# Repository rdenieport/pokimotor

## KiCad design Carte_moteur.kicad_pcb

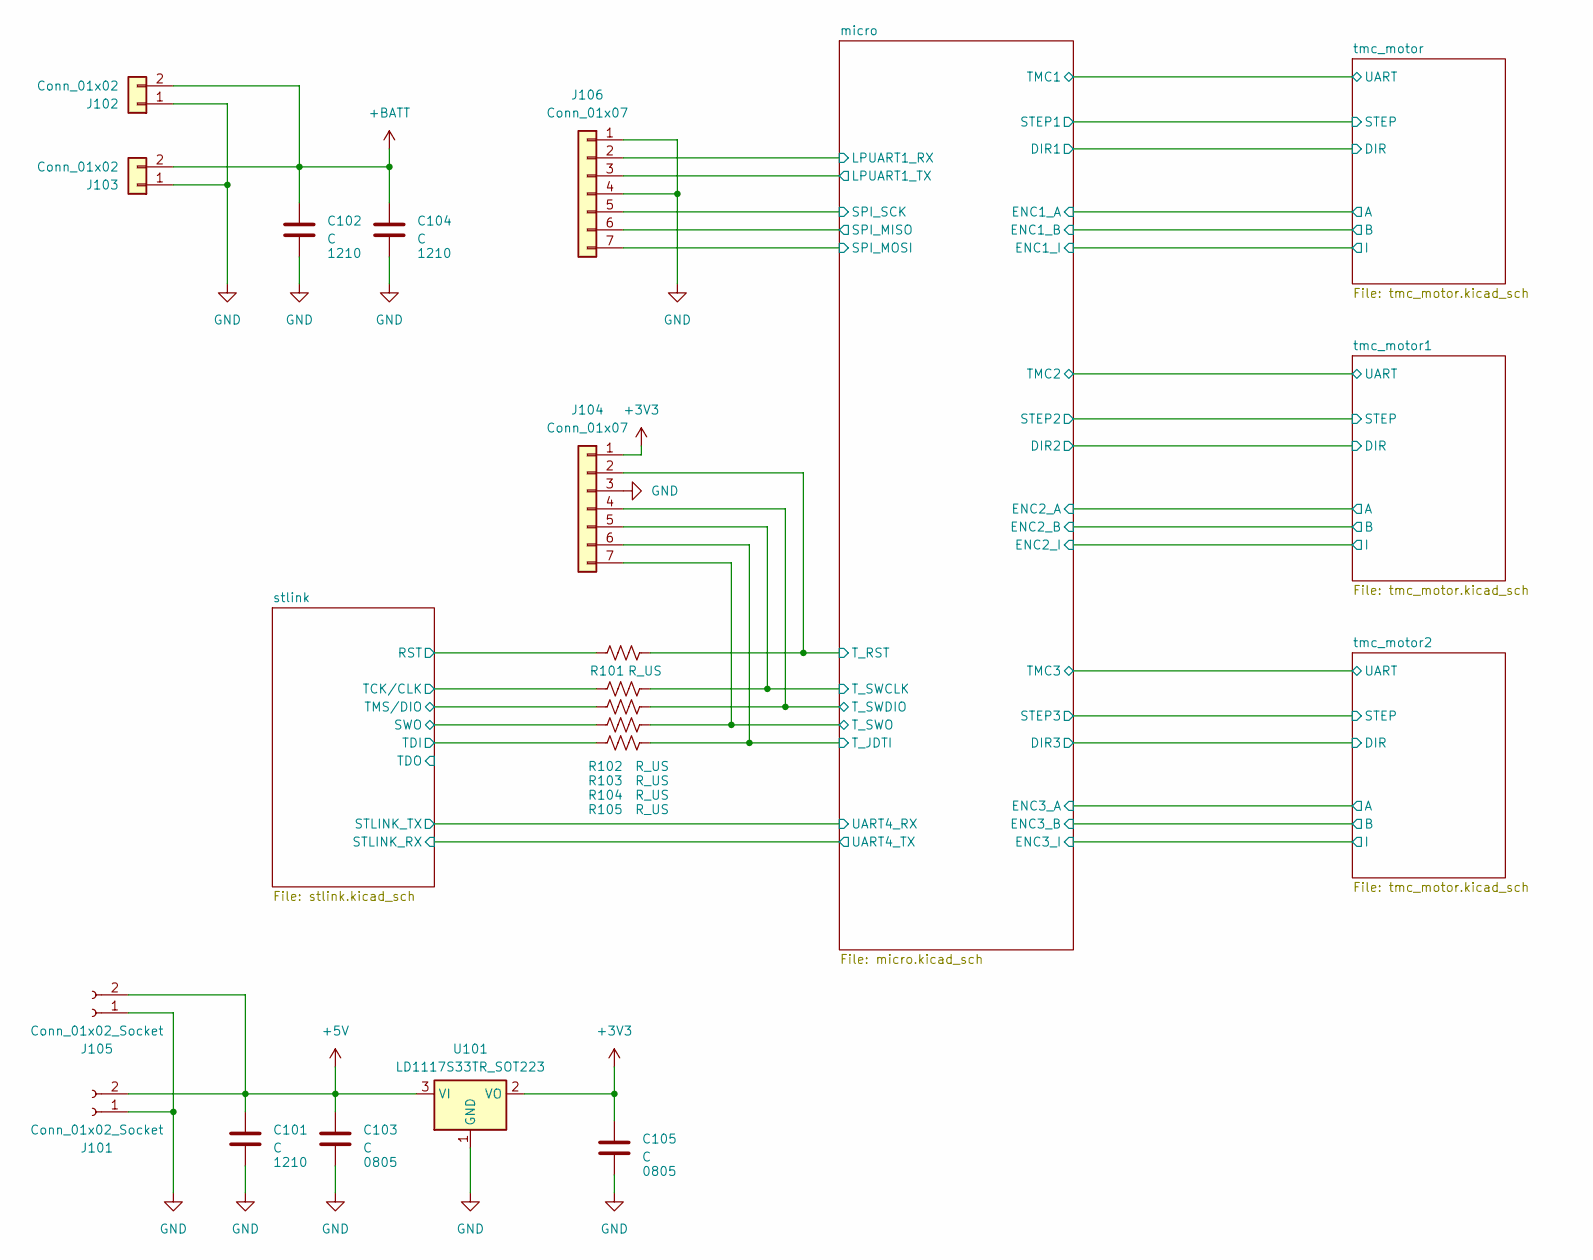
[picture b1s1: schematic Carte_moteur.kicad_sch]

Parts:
C101, C102, C104: C; C_1210_3225Metric_Pad1.33x2.70mm_HandSolder
C103, C105: C; C_0805_2012Metric_Pad1.18x1.45mm_HandSolder
J101, J105: Conn_01x02_Socket; Molex_KK-396_A-41791-0002_1x02_P3.96mm_Vertical
J102, J103: Conn_01x02; Molex_KK-396_A-41791-0002_1x02_P3.96mm_Vertical
J104, J106: Conn_01x07; Molex_KK-254_AE-6410-07A_1x07_P2.54mm_Vertical
R101, R102, R103, R104, R105: R_US; R_0603_1608Metric_Pad0.98x0.95mm_HandSolder
U101: LD1117S33TR_SOT223; SOT-223-3_TabPin2

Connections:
+3V3: C105.1, J104.1, U101.2 (VO); also elsewhere on the board
+5V: C101.1, C103.1, J101.2, J105.2, U101.3 (VI); also elsewhere on the board
+BATT: C102.1, C104.1, J102.2, J103.2; also elsewhere on the board
/micro/LPUART1_RX: J106.2; also elsewhere on the board
/micro/LPUART1_TX: J106.3; also elsewhere on the board
/micro/SPI1_MISO: J106.6; also elsewhere on the board
/micro/SPI1_MOSI: J106.7; also elsewhere on the board
/micro/SPI1_SCK: J106.5; also elsewhere on the board
/micro/T_JDTI: J104.6, R105.1; also elsewhere on the board
/micro/T_RST: J104.2, R101.1; also elsewhere on the board
/micro/T_SWCLK: J104.5, R102.1; also elsewhere on the board
/micro/T_SWDIO: J104.4, R103.1; also elsewhere on the board
/micro/T_SWO: J104.7, R104.1; also elsewhere on the board
/stlink/T_JTCK: R102.2; also elsewhere on the board
/stlink/T_JTDI: R105.2; also elsewhere on the board
/stlink/T_JTMS: R103.2; also elsewhere on the board
/stlink/T_NRST: R101.2; also elsewhere on the board
/stlink/T_SWO: R104.2; also elsewhere on the board
GND: C101.2, C102.2, C103.2, C104.2, C105.2, J101.1, J102.1, J103.1, J104.3, J105.1, J106.1, J106.4, U101.1 (GND); also elsewhere on the board

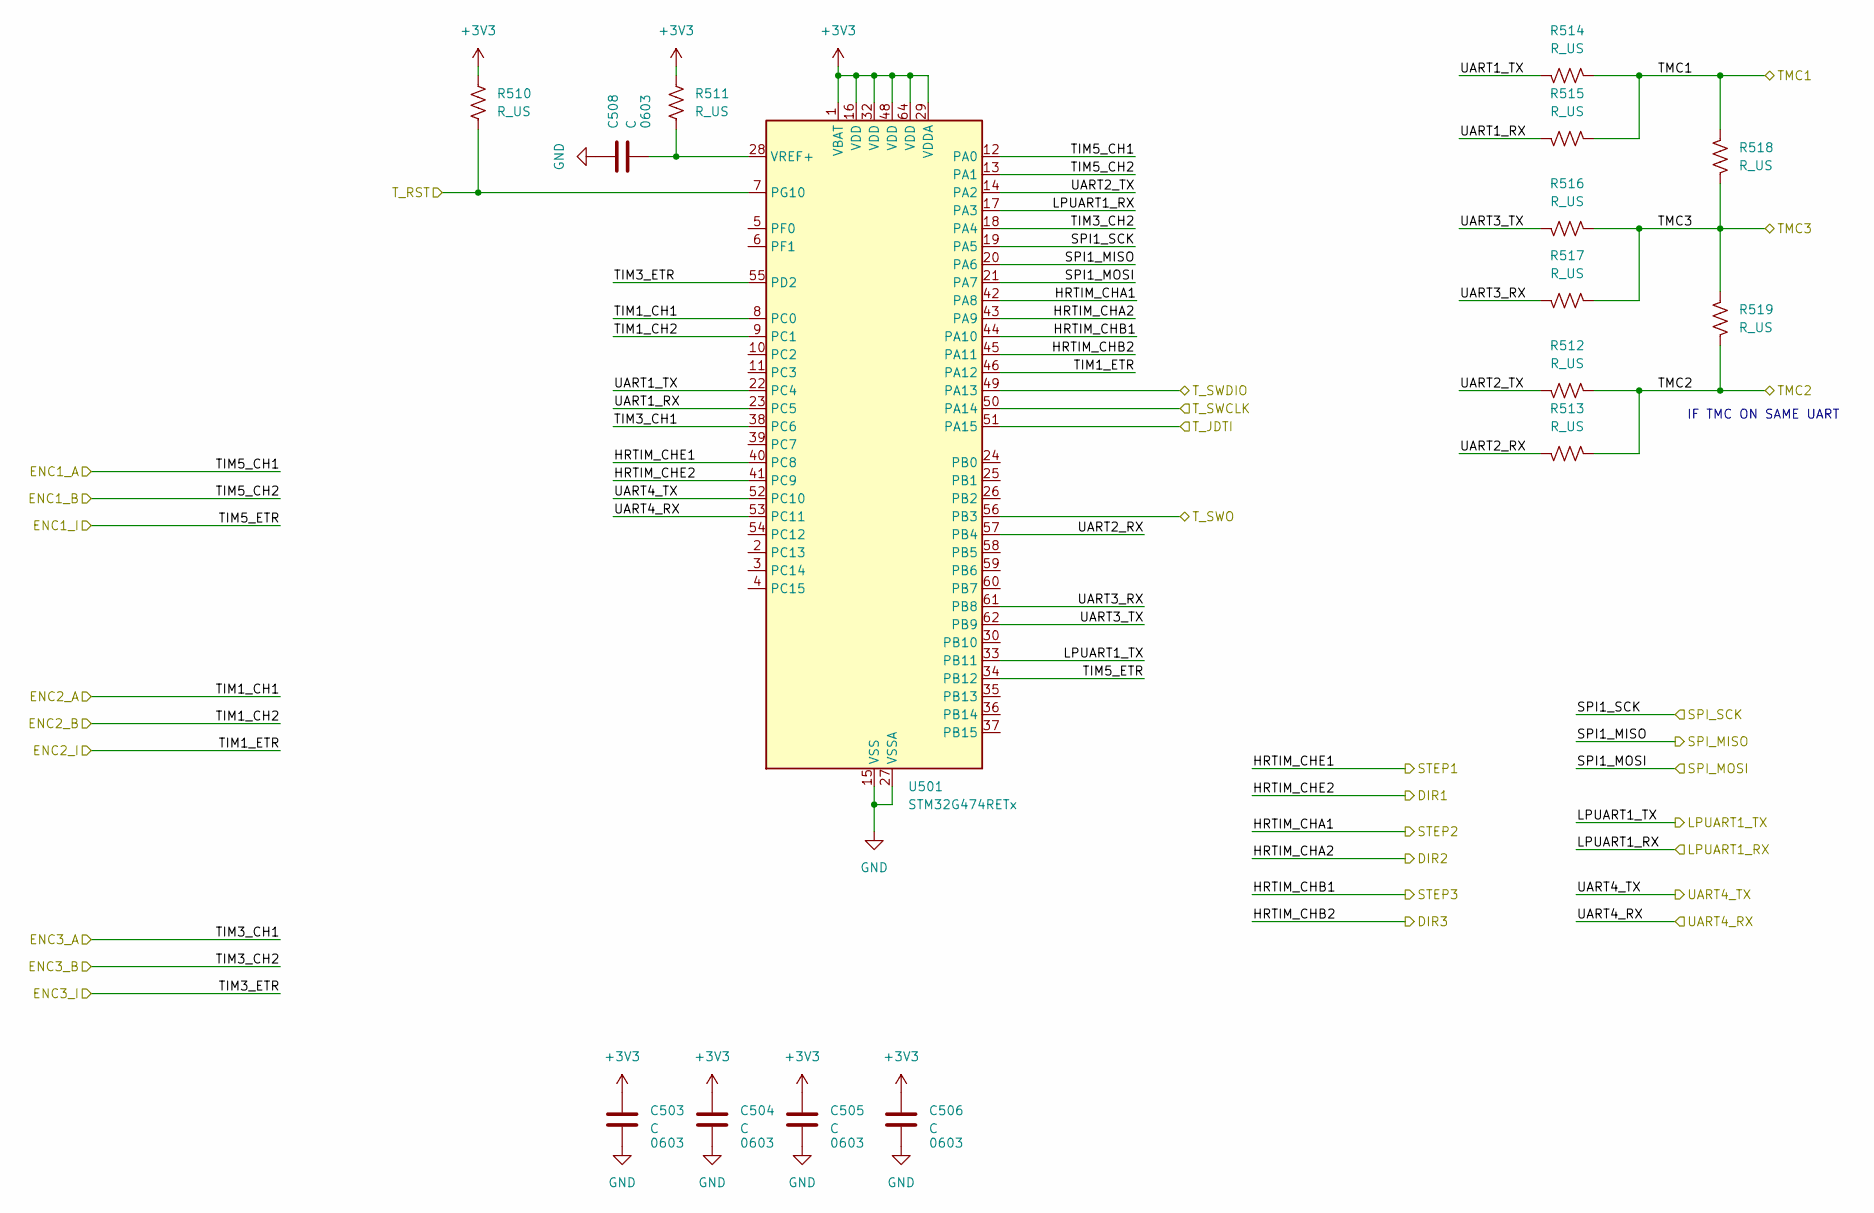
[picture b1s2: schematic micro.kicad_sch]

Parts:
C503, C504, C505, C506, C508: C; C_0603_1608Metric_Pad1.08x0.95mm_HandSolder
R510, R511, R512, R513, R514, R515, R516, R517: R_US; R_0603_1608Metric_Pad0.98x0.95mm_HandSolder
R518, R519: R_US; R_0805_2012Metric_Pad1.20x1.40mm_HandSolder
U501: STM32G474RETx; LQFP-64_10x10mm_P0.5mm

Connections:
+3V3: C503.1, C504.1, C505.1, C506.1, R510.2, R511.2, U501.1 (VBAT), U501.16 (VDD), U501.29 (VDDA), U501.32 (VDD), U501.48 (VDD), U501.64 (VDD); also elsewhere on the board
/micro/HRTIM_CHA1: U501.42 (PA8); also elsewhere on the board
/micro/HRTIM_CHA2: U501.43 (PA9); also elsewhere on the board
/micro/HRTIM_CHB1: U501.44 (PA10); also elsewhere on the board
/micro/HRTIM_CHB2: U501.45 (PA11); also elsewhere on the board
/micro/HRTIM_CHE1: U501.40 (PC8); also elsewhere on the board
/micro/HRTIM_CHE2: U501.41 (PC9); also elsewhere on the board
/micro/LPUART1_RX: U501.17 (PA3); also elsewhere on the board
/micro/LPUART1_TX: U501.33 (PB11); also elsewhere on the board
/micro/SPI1_MISO: U501.20 (PA6); also elsewhere on the board
/micro/SPI1_MOSI: U501.21 (PA7); also elsewhere on the board
/micro/SPI1_SCK: U501.19 (PA5); also elsewhere on the board
/micro/TIM1_CH1: U501.8 (PC0); also elsewhere on the board
/micro/TIM1_CH2: U501.9 (PC1); also elsewhere on the board
/micro/TIM1_ETR: U501.46 (PA12); also elsewhere on the board
/micro/TIM3_CH1: U501.38 (PC6); also elsewhere on the board
/micro/TIM3_CH2: U501.18 (PA4); also elsewhere on the board
/micro/TIM3_ETR: U501.55 (PD2); also elsewhere on the board
/micro/TIM5_CH1: U501.12 (PA0); also elsewhere on the board
/micro/TIM5_CH2: U501.13 (PA1); also elsewhere on the board
/micro/TIM5_ETR: U501.34 (PB12); also elsewhere on the board
/micro/TMC1: R514.1, R515.1, R518.1; also elsewhere on the board
/micro/TMC2: R512.1, R513.1, R519.2; also elsewhere on the board
/micro/TMC3: R516.1, R517.1, R518.2, R519.1; also elsewhere on the board
/micro/T_JDTI: U501.51 (PA15); also elsewhere on the board
/micro/T_RST: R510.1, U501.7 (PG10); also elsewhere on the board
/micro/T_SWCLK: U501.50 (PA14); also elsewhere on the board
/micro/T_SWDIO: U501.49 (PA13); also elsewhere on the board
/micro/T_SWO: U501.56 (PB3); also elsewhere on the board
/micro/UART1_RX: R515.2, U501.23 (PC5)
/micro/UART1_TX: R514.2, U501.22 (PC4)
/micro/UART2_RX: R513.2, U501.57 (PB4)
/micro/UART2_TX: R512.2, U501.14 (PA2)
/micro/UART3_RX: R517.2, U501.61 (PB8)
/micro/UART3_TX: R516.2, U501.62 (PB9)
/micro/UART4_RX: U501.53 (PC11); also elsewhere on the board
/micro/UART4_TX: U501.52 (PC10); also elsewhere on the board
GND: C503.2, C504.2, C505.2, C506.2, C508.1, U501.15 (VSS), U501.27 (VSSA), U501.31 (VSS), U501.47 (VSS), U501.63 (VSS); also elsewhere on the board
unnamed: C508.2, R511.1, U501.28 (VREF+)

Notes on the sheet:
IF TMC ON SAME UART

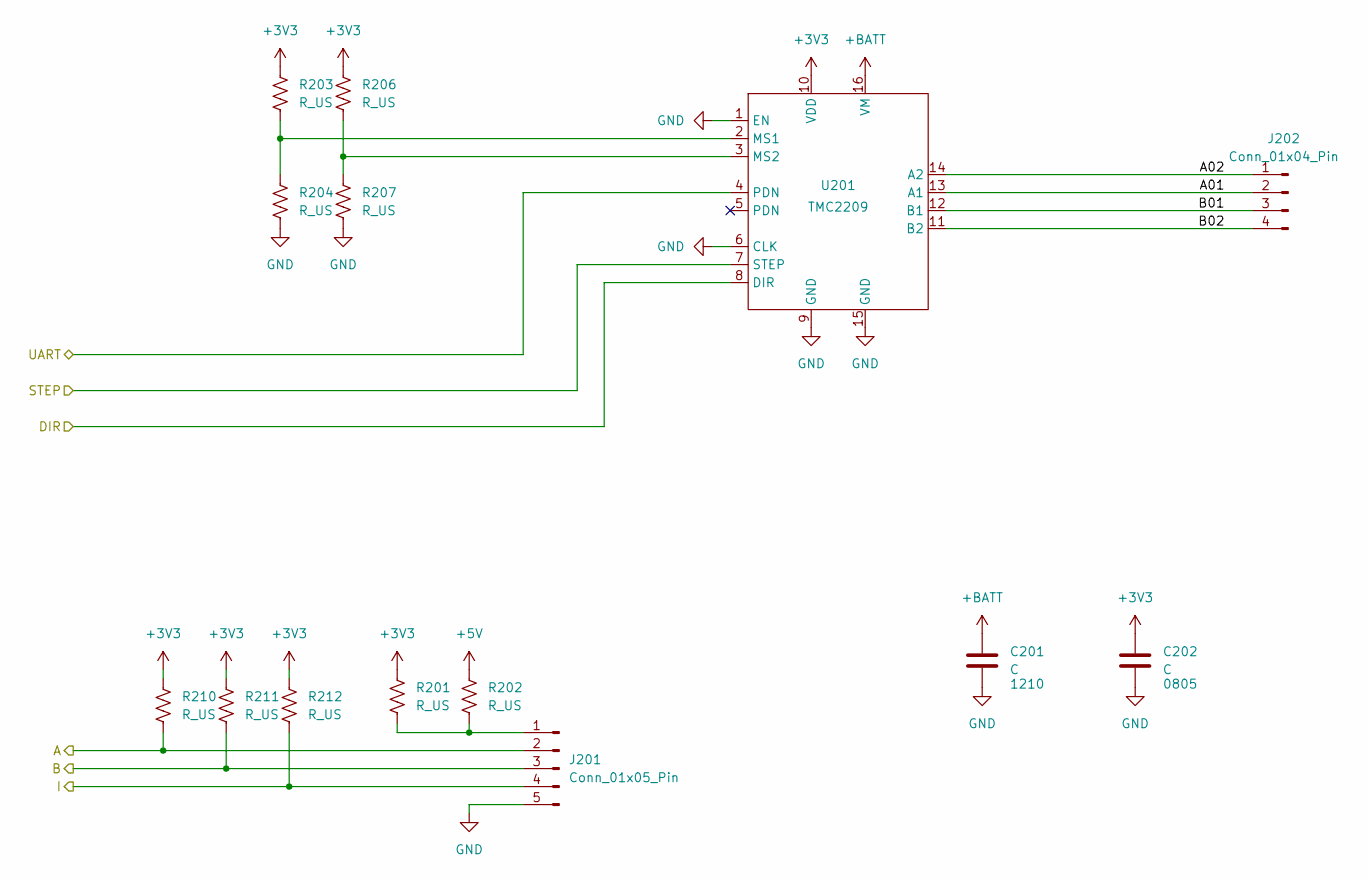
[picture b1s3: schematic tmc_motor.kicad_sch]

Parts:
C201: C; C_1210_3225Metric_Pad1.33x2.70mm_HandSolder
C202: C; C_0805_2012Metric_Pad1.18x1.45mm_HandSolder
J201: Conn_01x05_Pin; Molex_KK-254_AE-6410-05A_1x05_P2.54mm_Vertical
J202: Conn_01x04_Pin; Molex_KK-254_AE-6410-04A_1x04_P2.54mm_Vertical
R201, R202, R204, R207, R210, R211, R212: R_US; R_0603_1608Metric_Pad0.98x0.95mm_HandSolder
R203, R206: R_US; R_0805_2012Metric_Pad1.20x1.40mm_HandSolder
U201: TMC2209

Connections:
+3V3: C202.1, R201.2, R203.1, R206.1, R210.2, R211.2, R212.2, U201.10 (VDD); also elsewhere on the board
+5V: R202.2; also elsewhere on the board
+BATT: C201.1, U201.16 (VM); also elsewhere on the board
/micro/HRTIM_CHE1: U201.7 (STEP); also elsewhere on the board
/micro/HRTIM_CHE2: U201.8 (DIR); also elsewhere on the board
/micro/TIM5_CH1: J201.2, R210.1; also elsewhere on the board
/micro/TIM5_CH2: J201.3, R211.1; also elsewhere on the board
/micro/TIM5_ETR: J201.4, R212.1; also elsewhere on the board
/micro/TMC1: U201.4 (PDN); also elsewhere on the board
/tmc_motor/A01: J202.2, U201.13 (A1)
/tmc_motor/A02: J202.1, U201.14 (A2)
/tmc_motor/B01: J202.3, U201.12 (B1)
/tmc_motor/B02: J202.4, U201.11 (B2)
GND: C201.2, C202.2, J201.5, R204.2, R207.2, U201.1 (EN), U201.6 (CLK), U201.9 (GND), U201.15 (GND); also elsewhere on the board
unnamed: J201.1, R201.1, R202.1
unnamed: R203.2, R204.1, U201.2 (MS1)
unnamed: R206.2, R207.1, U201.3 (MS2)

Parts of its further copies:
C301, C401: C; C_1210_3225Metric_Pad1.33x2.70mm_HandSolder
C302, C402: C; C_0805_2012Metric_Pad1.18x1.45mm_HandSolder
J301, J401: Conn_01x05_Pin; Molex_KK-254_AE-6410-05A_1x05_P2.54mm_Vertical
J302, J402: Conn_01x04_Pin; Molex_KK-254_AE-6410-04A_1x04_P2.54mm_Vertical
R301, R302, R304, R307, R401, R402, R404, R407, R523, R524, R525, R526, R527, R528: R_US; R_0603_1608Metric_Pad0.98x0.95mm_HandSolder
R303, R306, R403, R406: R_US; R_0805_2012Metric_Pad1.20x1.40mm_HandSolder
U301, U401: TMC2209

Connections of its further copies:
+3V3: C302.1, C402.1, R301.2, R303.1, R306.1, R401.2, R403.1, R406.1, R523.2, R524.2, R525.2, R526.2, R527.2, R528.2, U301.10 (VDD), U401.10 (VDD); also elsewhere on the board
+5V: R302.2, R402.2; also elsewhere on the board
+BATT: C301.1, C401.1, U301.16 (VM), U401.16 (VM); also elsewhere on the board
/micro/HRTIM_CHA1: U301.7 (STEP); also elsewhere on the board
/micro/HRTIM_CHA2: U301.8 (DIR); also elsewhere on the board
/micro/HRTIM_CHB1: U401.7 (STEP); also elsewhere on the board
/micro/HRTIM_CHB2: U401.8 (DIR); also elsewhere on the board
/micro/TIM1_CH1: J301.2, R523.1; also elsewhere on the board
/micro/TIM1_CH2: J301.3, R524.1; also elsewhere on the board
/micro/TIM1_ETR: J301.4, R525.1; also elsewhere on the board
/micro/TIM3_CH1: J401.2, R526.1; also elsewhere on the board
/micro/TIM3_CH2: J401.3, R527.1; also elsewhere on the board
/micro/TIM3_ETR: J401.4, R528.1; also elsewhere on the board
/micro/TMC2: U301.4 (PDN); also elsewhere on the board
/micro/TMC3: U401.4 (PDN); also elsewhere on the board
/tmc_motor1/A01: J302.2, U301.13 (A1)
/tmc_motor1/A02: J302.1, U301.14 (A2)
/tmc_motor1/B01: J302.3, U301.12 (B1)
/tmc_motor1/B02: J302.4, U301.11 (B2)
/tmc_motor2/A01: J402.2, U401.13 (A1)
/tmc_motor2/A02: J402.1, U401.14 (A2)
/tmc_motor2/B01: J402.3, U401.12 (B1)
/tmc_motor2/B02: J402.4, U401.11 (B2)
GND: C301.2, C302.2, C401.2, C402.2, J301.5, J401.5, R304.2, R307.2, R404.2, R407.2, U301.1 (EN), U301.6 (CLK), U301.9 (GND), U301.15 (GND), U401.1 (EN), U401.6 (CLK), U401.9 (GND), U401.15 (GND); also elsewhere on the board
unnamed: J301.1, R301.1, R302.1
unnamed: J401.1, R401.1, R402.1
unnamed: R303.2, R304.1, U301.2 (MS1)
unnamed: R306.2, R307.1, U301.3 (MS2)
unnamed: R403.2, R404.1, U401.2 (MS1)
unnamed: R406.2, R407.1, U401.3 (MS2)

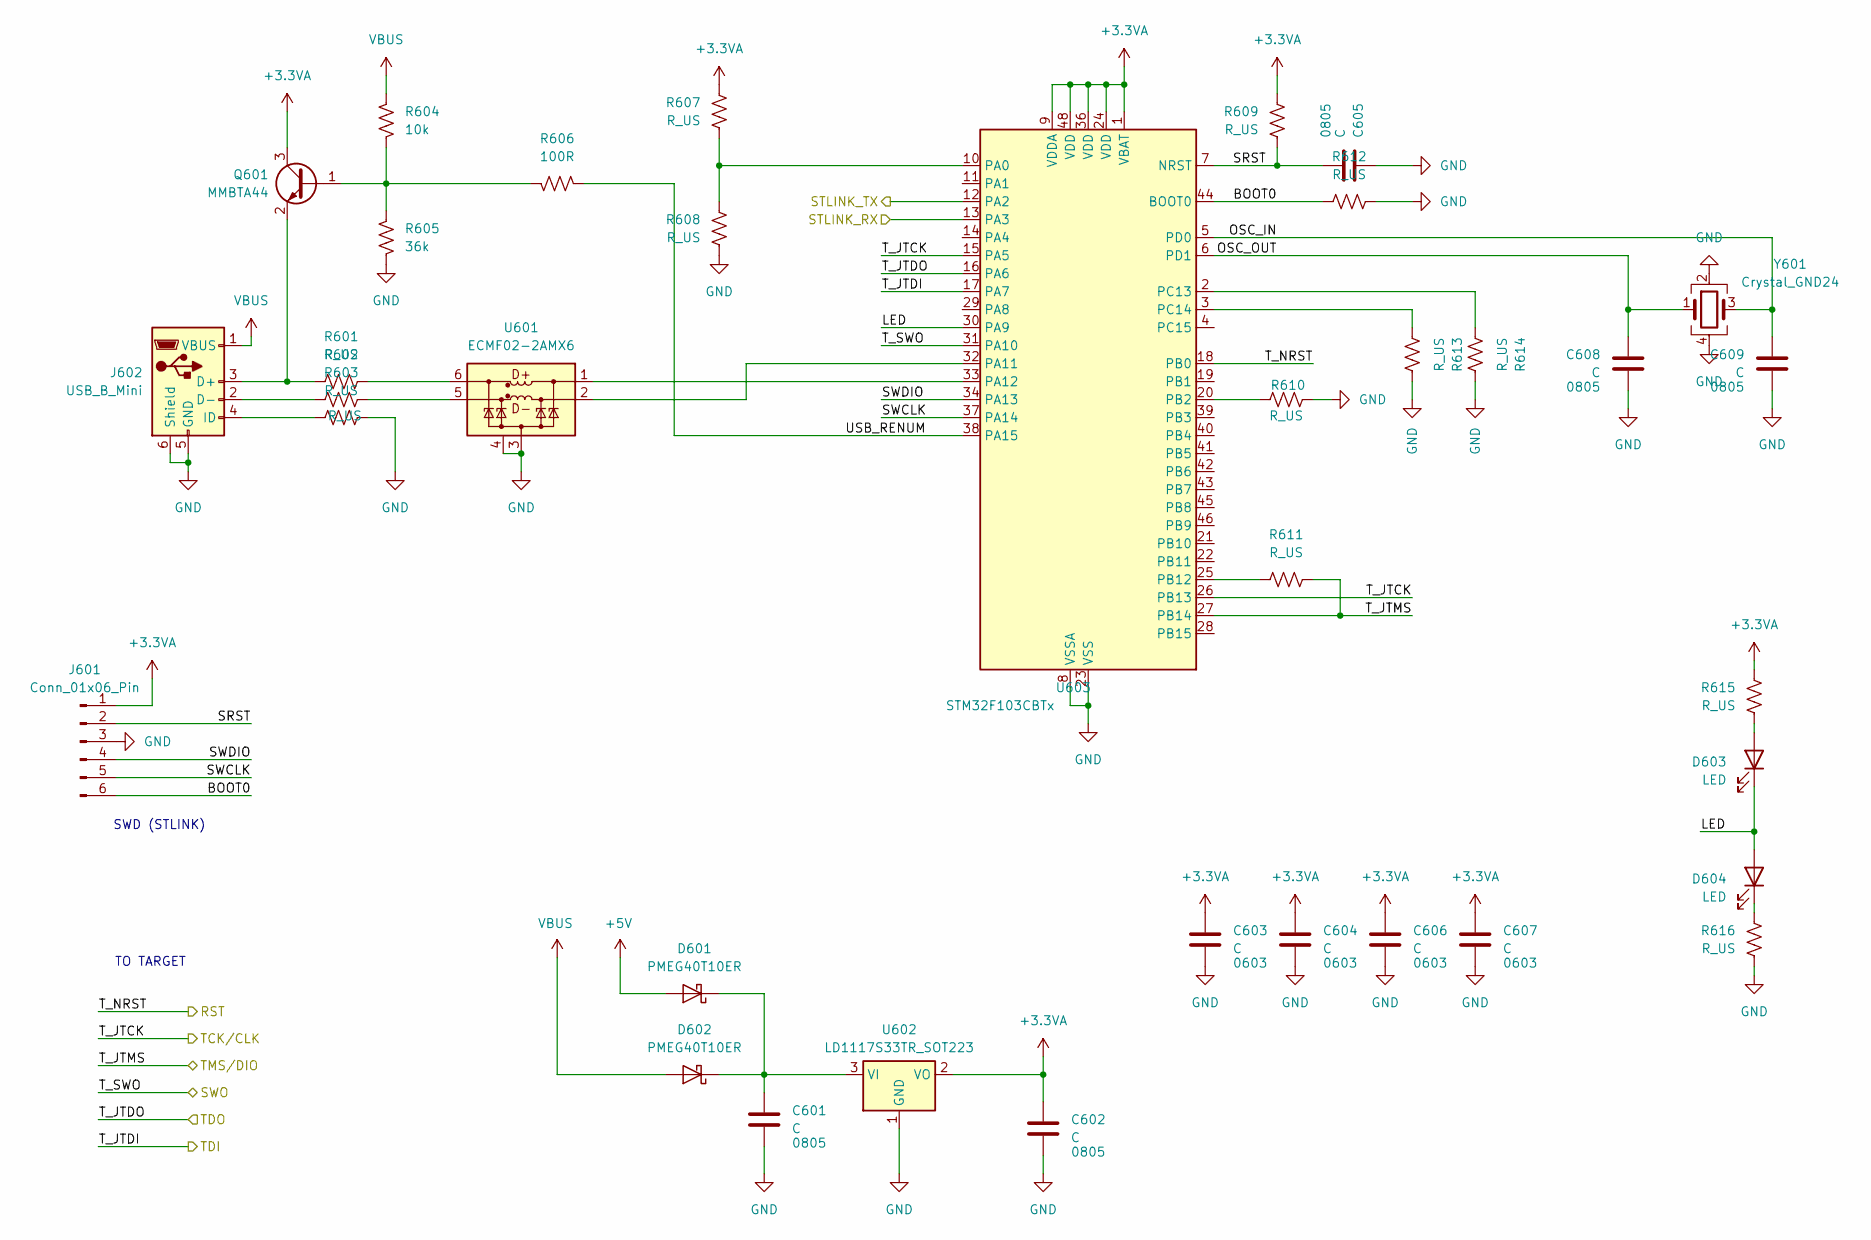
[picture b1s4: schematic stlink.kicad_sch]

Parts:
C601, C602, C605, C608, C609: C; C_0805_2012Metric_Pad1.18x1.45mm_HandSolder
C603, C604, C606, C607: C; C_0603_1608Metric_Pad1.08x0.95mm_HandSolder
D601, D602: PMEG40T10ER; Nexperia_CFP3_SOD-123W
D603, D604: LED; LED_0805_2012Metric_Pad1.15x1.40mm_HandSolder
J601: Conn_01x06_Pin; PinHeader_1x06_P2.54mm_Vertical
J602: USB_B_Mini; USB_Micro-B_Wuerth_629105150521
Q601: MMBTA44; SOT-23
R601, R602, R603, R607, R608, R609, R610, R611, R612, R613, R614, R615, R616: R_US; R_0603_1608Metric_Pad0.98x0.95mm_HandSolder
R604: 10k; R_0603_1608Metric_Pad0.98x0.95mm_HandSolder
R605: 36k; R_0603_1608Metric_Pad0.98x0.95mm_HandSolder
R606: 100R; R_0603_1608Metric_Pad0.98x0.95mm_HandSolder
U601: ECMF02-2AMX6; ST_UQFN-6L_1.5x1.7mm_P0.5mm
U602: LD1117S33TR_SOT223; SOT-223-3_TabPin2
U603: STM32F103CBTx; LQFP-48_7x7mm_P0.5mm
Y601: Crystal_GND24; Crystal_SMD_EuroQuartz_MQ-4Pin_7.0x5.0mm_HandSoldering

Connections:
+3.3VA: C602.1, C603.1, C604.1, C606.1, C607.1, J601.1, Q601.3 (C), R607.1, R609.1, R615.1, U602.2 (VO), U603.1 (VBAT), U603.9 (VDDA), U603.24 (VDD), U603.36 (VDD), U603.48 (VDD)
+5V: D601.2 (A); also elsewhere on the board
/micro/UART4_RX: U603.12 (PA2); also elsewhere on the board
/micro/UART4_TX: U603.13 (PA3); also elsewhere on the board
/stlink/BOOT0: J601.6, R612.1, U603.44 (BOOT0)
/stlink/LED: D603.1 (K), D604.2 (A), U603.30 (PA9)
/stlink/OSC_IN: C609.1, U603.5 (PD0), Y601.3
/stlink/OSC_OUT: C608.1, U603.6 (PD1), Y601.1
/stlink/SRST: C605.2, J601.2, R609.2, U603.7 (NRST)
/stlink/SWCLK: J601.5, U603.37 (PA14)
/stlink/SWDIO: J601.4, U603.34 (PA13)
/stlink/T_JTCK: U603.15 (PA5), U603.26 (PB13); also elsewhere on the board
/stlink/T_JTDI: U603.17 (PA7); also elsewhere on the board
/stlink/T_JTDO: U603.16 (PA6)
/stlink/T_JTMS: R611.2, U603.27 (PB14); also elsewhere on the board
/stlink/T_NRST: U603.18 (PB0); also elsewhere on the board
/stlink/T_SWO: U603.31 (PA10); also elsewhere on the board
/stlink/USB_RENUM: R606.1, U603.38 (PA15)
GND: C601.2, C602.2, C603.2, C604.2, C605.1, C606.2, C607.2, C608.2, C609.2, J601.3, J602.5 (GND), J602.6 (Shield), R603.2, R605.2, R608.2, R610.2, R612.2, R613.2, R614.2, R616.2, U601.3 (GND), U601.4 (NC), U602.1 (GND), U603.8 (VSSA), U603.23 (VSS), U603.35 (VSS), U603.47 (VSS), Y601.2, Y601.4; also elsewhere on the board
unnamed: C601.1, D601.1 (K), D602.1 (K), U602.3 (VI)
unnamed: D603.2 (A), R615.2
unnamed: D604.1 (K), R616.1
unnamed: J602.3 (D+), Q601.2 (E), R601.1
unnamed: J602.2 (D-), R602.1
unnamed: J602.4 (ID), R603.1
unnamed: Q601.1 (B), R604.2, R605.1, R606.2
unnamed: U601.1 (D+_in), U603.33 (PA12)
unnamed: R601.2, U601.6 (D+_out)
unnamed: U601.2 (D-_in), U603.32 (PA11)
unnamed: R602.2, U601.5 (D-_out)
unnamed: R607.2, R608.1, U603.10 (PA0)
unnamed: R610.1, U603.20 (PB2)
unnamed: R611.1, U603.25 (PB12)
unnamed: R614.1, U603.2 (PC13)
unnamed: R613.1, U603.3 (PC14)
VBUS: D602.2 (A), J602.1 (VBUS), R604.1

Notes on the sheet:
TO TARGET
SWD (STLINK)

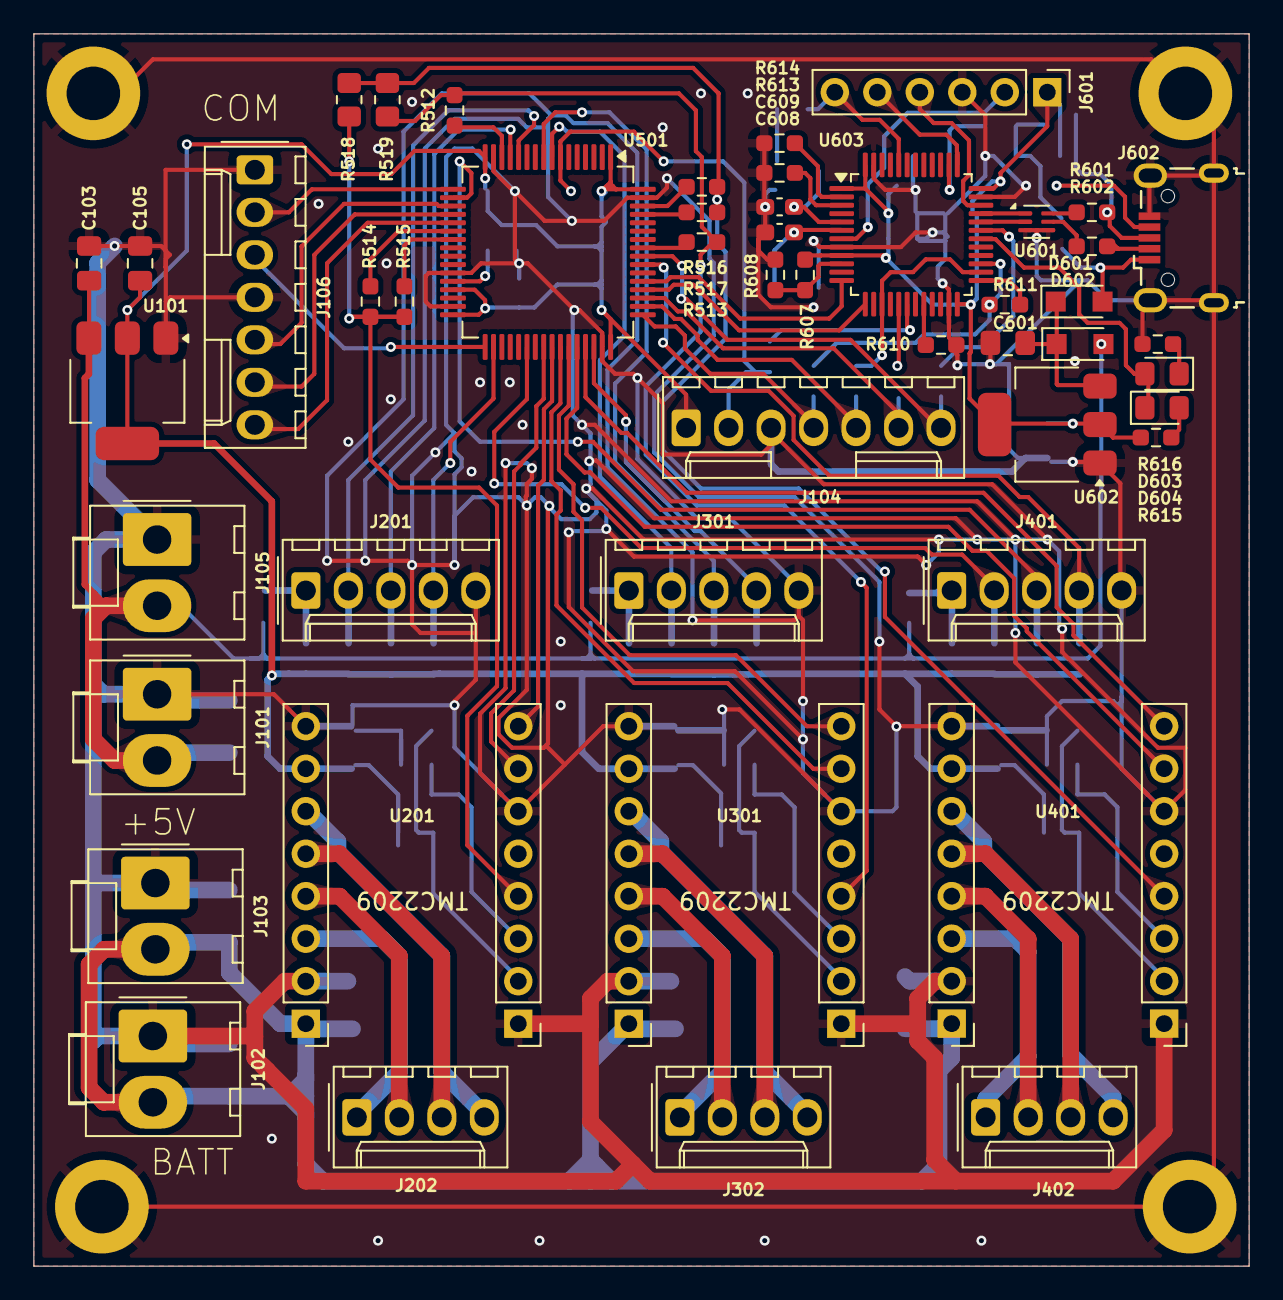
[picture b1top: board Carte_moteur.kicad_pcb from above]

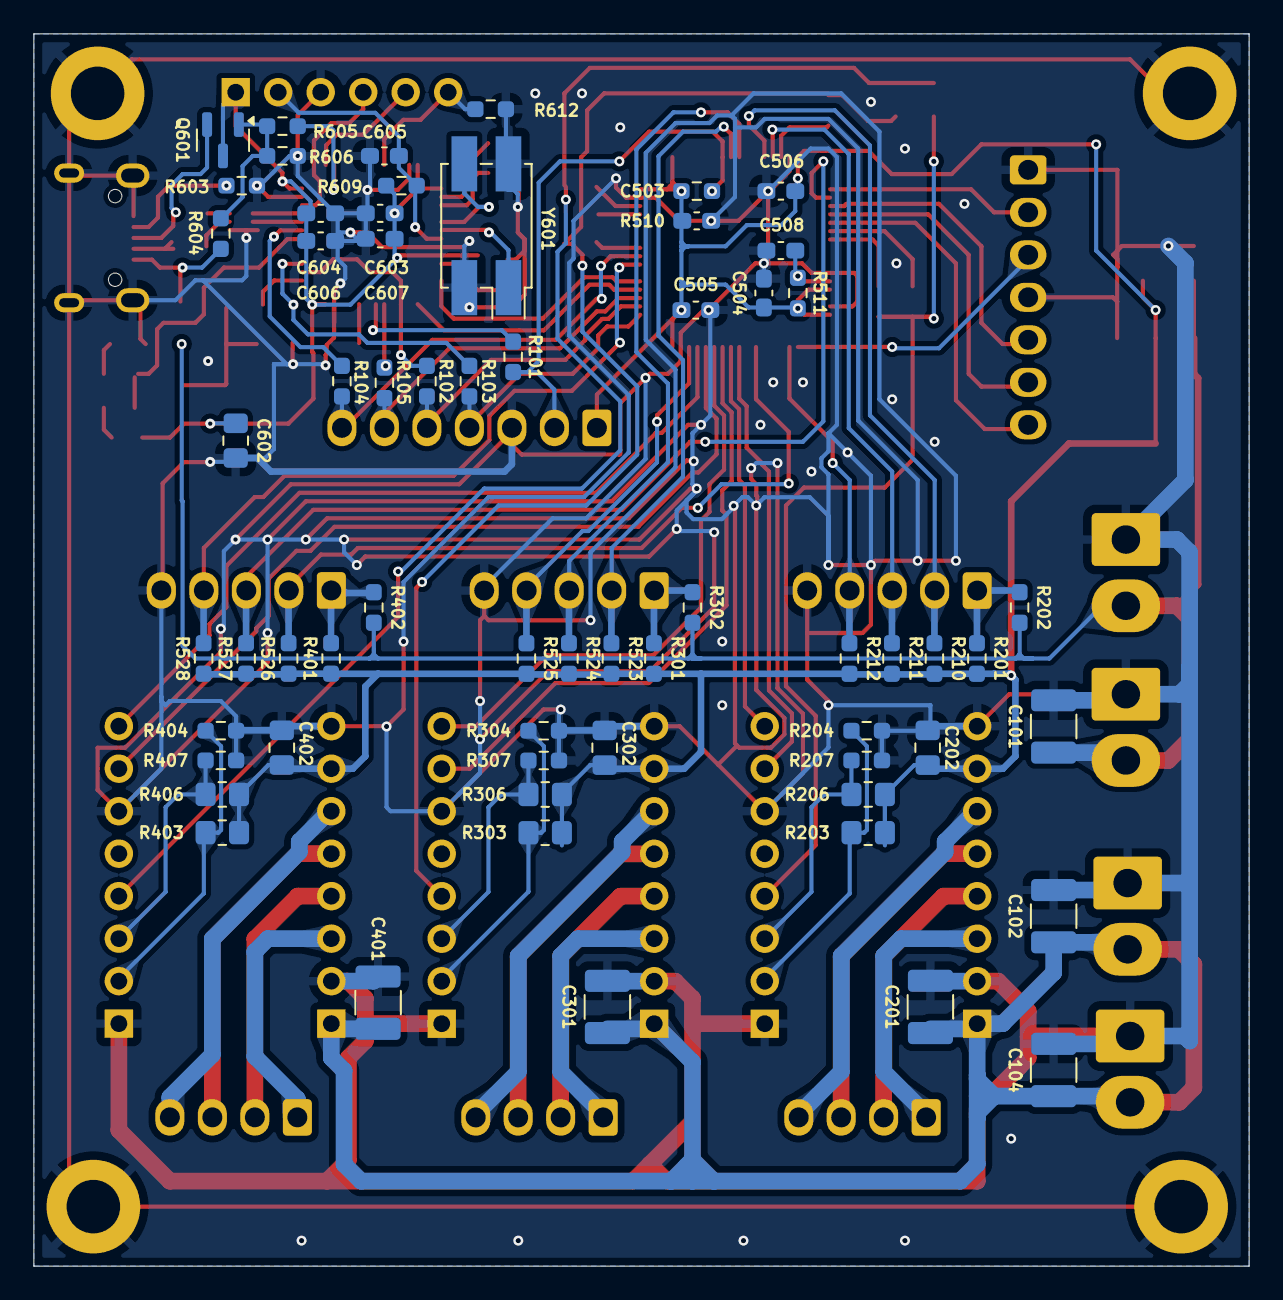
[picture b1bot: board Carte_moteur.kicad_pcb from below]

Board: 2 copper layers, 72.6 x 73.7 mm, 115 parts (62 on the bottom side), 93 nets.

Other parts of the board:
H101, H102, H103, H104: MountingHole_Pad; MountingHole_3.2mm_M3_DIN965_Pad

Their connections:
GND: H101.1, H102.1, H103.1, H104.1; also elsewhere on the board

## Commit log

2025-02-23 initial commit. First version of schematic
2025-02-23 Added SPI
2025-02-23 starting layout
2025-02-24 quadrature encoder added
2025-02-26 Add net class
2025-03-01 move encoder pull up resistor to tmc sheet
2025-03-01 hrtim
2025-03-01 AHHHAHAHAHHAH
2025-03-01 reduced stlink size
2025-03-02 before trying new µC orientation
2025-03-02 almost done
2025-03-02 tracks done
2025-03-02 silk and holes ok
2025-03-02 ready for manufacturing
2025-03-02 remove wierd angles
